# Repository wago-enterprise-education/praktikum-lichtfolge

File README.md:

# Praktikum – Lichtfolge

Bau einer kleinen Platine als handheld Spielekonsole.

- **Dauer:** ~20 Min. (ohne Auf- und Abbbauzeit)

</br>

## Quick Links
- **Dokumentation:** [wago-enterprise-education.github.io/praktikum-lichtfolge/](https://wago-enterprise-education.github.io/praktikum-lichtfolge/)
- **Bestückungsplan:** [docs/Bestueckungsplan_praktikum-lichtfolge_v1.0.html](https://wago-enterprise-education.github.io/praktikum-lichtfolge/Bestueckungsplan_praktikum-lichtfolge_v1.0.html)
- **Schaltplan:** [pcb/schematics_praktikum-lichtfolge.pdf](pcb/schematics_praktikum-lichtfolge.pdf)
- **Materialliste (BOM):** [docs/bom/ibom_praktikum-lichtfolge_v1.0.html](https://wago-enterprise-education.github.io/praktikum-lichtfolge/bom/ibom_praktikum-lichtfolge_v1.0.html)

## Ansprechpartner
- [Tobias Lauxtermann](mailto:tobias.lauxtermann@wago.com)

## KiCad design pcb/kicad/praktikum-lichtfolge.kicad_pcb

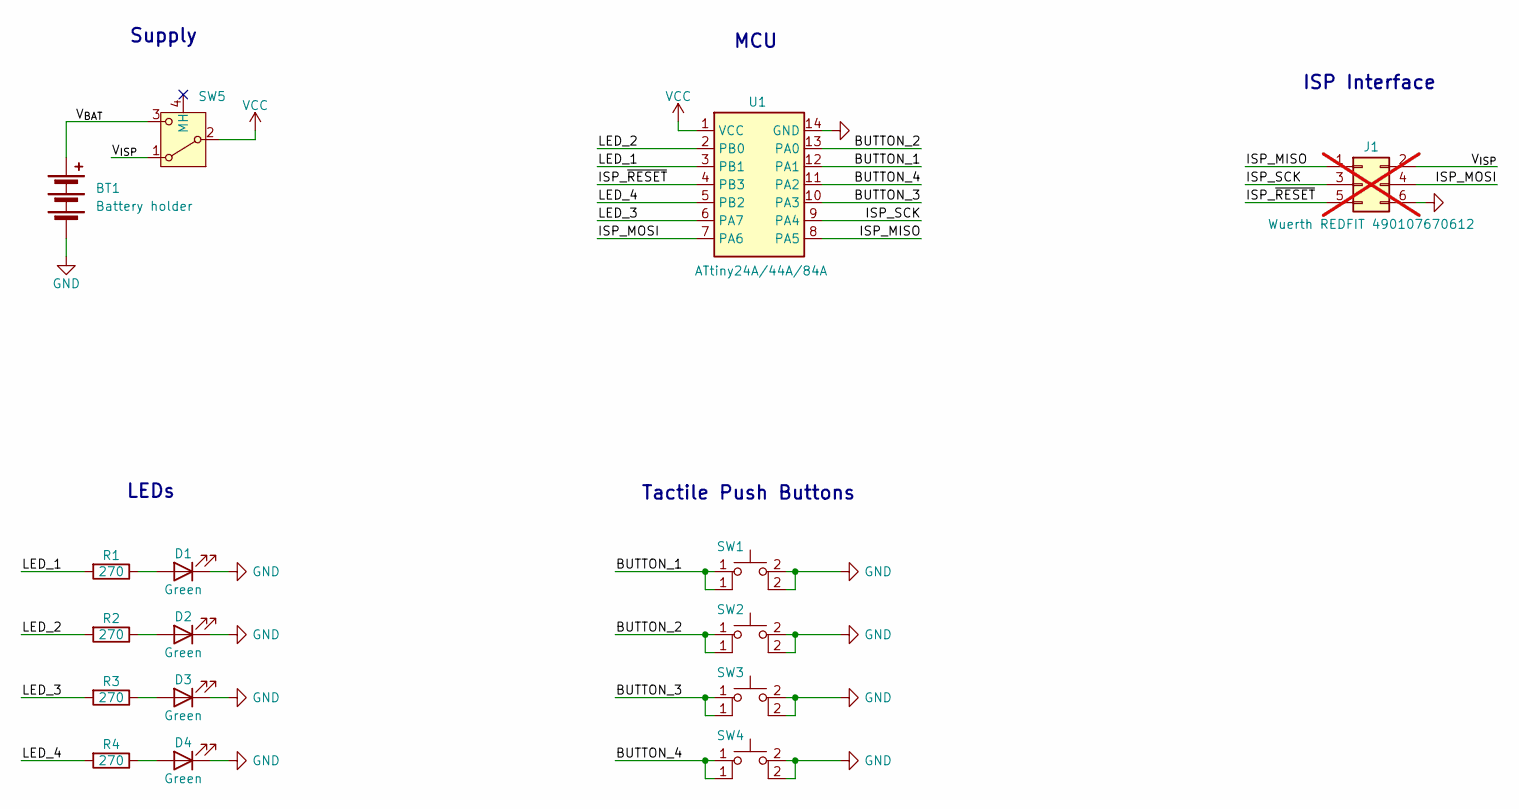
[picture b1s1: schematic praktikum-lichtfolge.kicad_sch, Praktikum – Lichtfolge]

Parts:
BT1: Battery holder; Keystone_3x_AA_battery_holder_2464; MPN 185-4644
D1, D2, D3, D4: Green; LED_D5.0mm; MPN L-53GD
J1: Wuerth REDFIT 490107670612; Wuerth_REDFIT_490107670612; MPN 490107670612; not fitted
R1, R2, R3, R4: 270; R_Axial_DIN0207_L6.3mm_D2.5mm_P10.16mm_Horizontal; MPN CFR50J270R
SW1, SW2, SW3, SW4: SW_Tactile_6mm; SW_PUSH_6mm_H5mm; MPN 1825910-6
SW5: SPDT_slide_switch; MPN 1386942
U1: ATtiny24A/44A/84A; DIP-14_W7.62mm; MPN ATTINY84A-PU

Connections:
/BUTTON_1: SW1.1, U1.12 (PA1)
/BUTTON_2: SW2.1, U1.13 (PA0)
/BUTTON_3: SW3.1, U1.10 (PA3)
/BUTTON_4: SW4.1, U1.11 (PA2)
/ISP_MISO: J1.1, U1.8 (PA5)
/ISP_MOSI: J1.4, U1.7 (PA6)
/ISP_SCK: J1.3, U1.9 (PA4)
/ISP_~RESET: J1.5, U1.4 (PB3)
/LED_1: R1.2, U1.3 (PB1)
/LED_2: R2.2, U1.2 (PB0)
/LED_3: R3.2, U1.6 (PA7)
/LED_4: R4.2, U1.5 (PB2)
/V_{BAT}: BT1.1 (+), SW5.3
/V_{ISP}: J1.2, SW5.1
GND: BT1.2 (-), D1.1 (K), D2.1 (K), D3.1 (K), D4.1 (K), J1.6, SW1.2, SW2.2, SW3.2, SW4.2, U1.14 (GND)
unnamed: D1.2 (A), R1.1
unnamed: D2.2 (A), R2.1
unnamed: D3.2 (A), R3.1
unnamed: D4.2 (A), R4.1
VCC: SW5.2, U1.1 (VCC)

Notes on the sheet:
ISP Interface
Supply
LEDs
MCU
Tactile Push Buttons

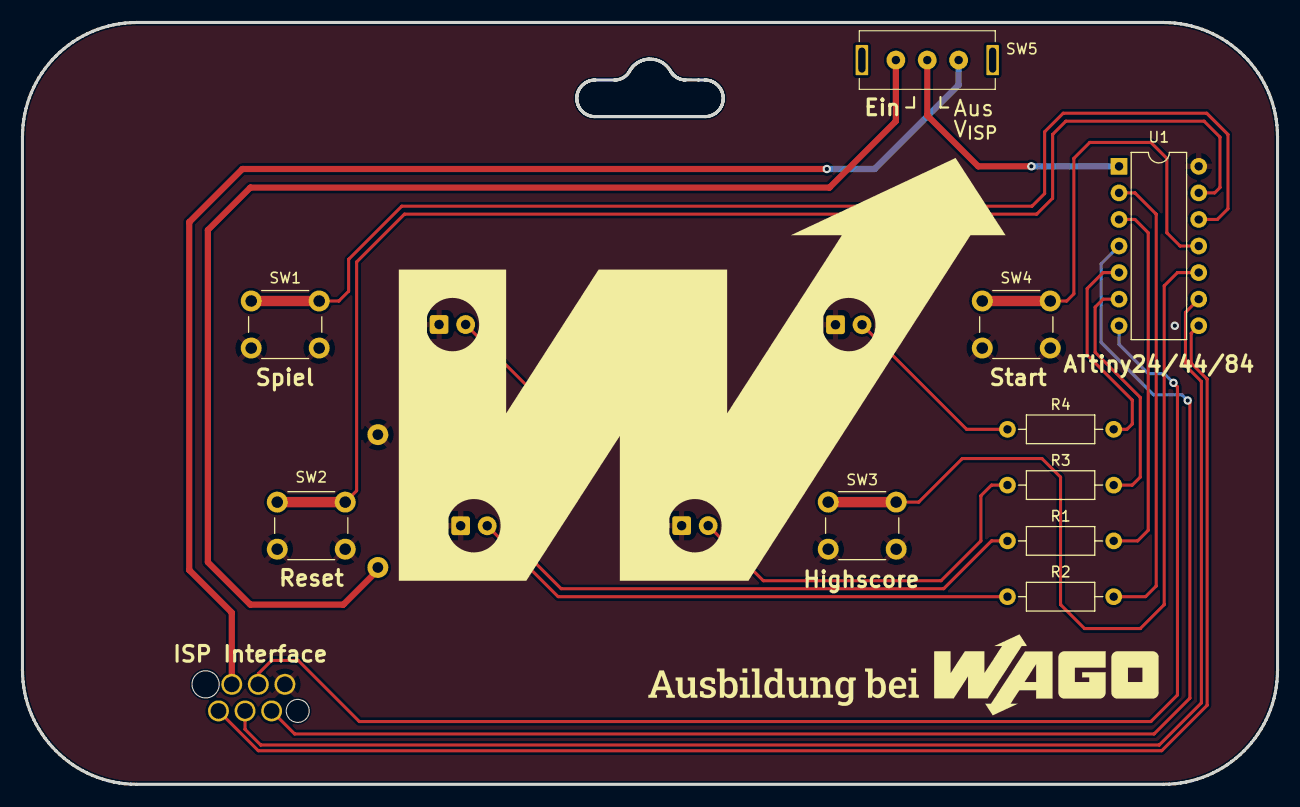
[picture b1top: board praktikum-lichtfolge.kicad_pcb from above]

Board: 2 copper layers, 120.0 x 72.8 mm, 16 parts (1 on the bottom side), 20 nets.

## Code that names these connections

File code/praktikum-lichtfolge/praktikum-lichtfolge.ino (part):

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#define WHACK_A_MOLE_GAME_DURATION 30000

// Pin assignments (see Pinout_x4.jpg)
uint8_t leds[] = {PIN_PB1, PIN_PB0, PIN_PA7, PIN_PB2};
uint8_t buttonPins[] = {PIN_PA1, PIN_PA0, PIN_PA3, PIN_PA2};

/*
// Breadboard setup
uint8_t leds[] = {PIN_PA7, PIN_PB2, PIN_PB1, PIN_PB0};
uint8_t buttonPins[] = {PIN_PA3, PIN_PA2, PIN_PA1, PIN_PA0};
*/

Bounce2::Button buttons[4]; // Create 4 button objects
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  initEEPROM(); // Reset EEPROM on first start

  // Seed the pseudo random number generator 
  pinMode(A1, INPUT); // Use ADC1 which is also PIN_PA1 where the first button is connected to since there is no unused pin left
  delay(100);
  uint16_t seedVal = analogRead(A1);
  while(seedVal == 0) { // Don't seed the pseudo random number generator as long as the button is pressed to prevent cheating
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
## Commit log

2025-06-26 Add folders, files from v1.0 and documentation
2025-06-26 Rename folder
2025-06-26 Correct typo
2025-06-27 Some corrections
